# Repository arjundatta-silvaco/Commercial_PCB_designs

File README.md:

# Commercial PCB designs

A repository with circuits schematics and PCB designs of breakout boards.

Check out my blog: [https://semicon.world/](https://semicon.world/)

Support the blog and the GitHub: [https://razorpay.me/@semiconworld](https://razorpay.me/@semiconworld)

### License Notice: This repository is provided for personal study and educational reference. Research publication, commercial use, redistribution, and reuse of repository contents require prior permission. See the LICENSE file for details.

#### Currently in the Repository:

* LM2596S-adj Buck converter 9-12.9V to 5V 3A: Complete
* TP5100 Battery Charger 2S: Complete
* HX-2S-JH20: Complete
* HUSB238 USB-C Power Delivery: Complete
* ESP-32 DEVKIT V1 WROOM-32: Planned

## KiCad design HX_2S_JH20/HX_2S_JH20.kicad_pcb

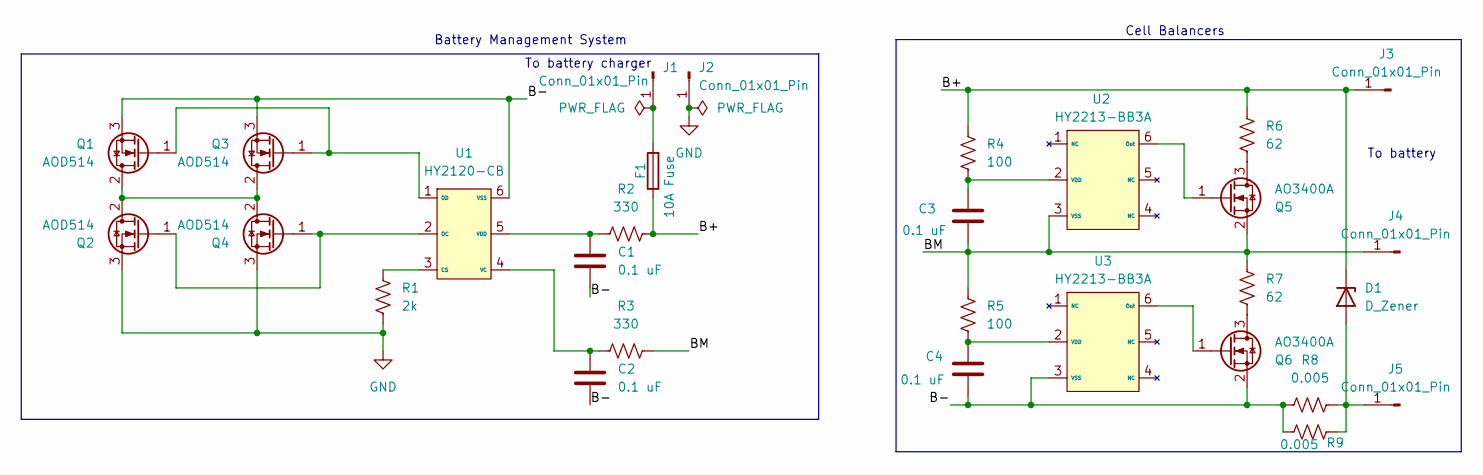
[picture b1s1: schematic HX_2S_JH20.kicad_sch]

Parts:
C1, C2, C3, C4: 0.1 uF; C_0603_1608Metric; Part number GRM188R61E104KA01D
D1: D_Zener; D_SOD-123; Part number MMSZ9V1T1G
F1: 10A Fuse; Fuse_0603_1608Metric; Part number 0685H9100-01
J1, J2, J3, J5: Conn_01x01_Pin; SolderWire-4sqmm_1x01_D3mm_OD6mm; Part number Bare pad
J4: Conn_01x01_Pin; SolderWire-2sqmm_1x01_D2mm_OD3.9mm; Part number Bare pad
Q1, Q2, Q3, Q4: AOD514; TO-252-2; Part number AOD514
Q5, Q6: AO3400A; SOT-23; Part number AO3400A
R1: 2k; R_0603_1608Metric; Part number ERJ-3EKF2001V
R2, R3: 330; R_0603_1608Metric; Part number ERJ-3GEYJ331V
R4, R5: 100; R_0603_1608Metric; Part number ESR03EZPF1000
R6, R7: 62; R_2512_6332Metric; Part number ERJ-1TYJ620U
R8, R9: 0.005; R_2512_6332Metric; Part number CRE2512-FZ-R005E-2
U1: HY2120-CB; SOT-23-6; Part number HY2120-CB
U2, U3: HY2213-BB3A; SOT-23-6; Part number HY2213-BB3A

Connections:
/B+: D1.1 (K), F1.1, J3.1 (Pin_1_1), R2.2, R4.1, R6.1
/B-: C1.2, C2.2, C4.2, Q1.3 (S), Q3.3 (S), Q6.2 (S), R8.1, R9.1, U1.6 (VSS), U3.3 (VSS)
/BM: C3.2, J4.1 (Pin_1_1), Q5.2 (S), R3.2, R5.1, R7.1, U2.3 (VSS)
GND: J2.1 (Pin_1_1), Q2.3 (S), Q4.3 (S), R1.2
unnamed: D1.2 (A), J5.1 (Pin_1_1), R8.2, R9.2
unnamed: F1.2, J1.1 (Pin_1_1)
unnamed: Q1.2 (D), Q2.2 (D), Q3.2 (D), Q4.2 (D)
unnamed: Q1.1 (G), Q3.1 (G), U1.1 (OD)
unnamed: Q2.1 (G), Q4.1 (G), U1.2 (OC)
unnamed: Q5.3 (D), R6.2
unnamed: Q5.1 (G), U2.6 (Out)
unnamed: Q6.3 (D), R7.2
unnamed: Q6.1 (G), U3.6 (Out)
unnamed: R1.1, U1.3 (CS)
unnamed: C2.1, R3.1, U1.4 (VC)
unnamed: C1.1, R2.1, U1.5 (VDD)
unnamed: C3.1, R4.2, U2.2 (VDD)
unnamed: C4.1, R5.2, U3.2 (VDD)

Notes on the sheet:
To battery
Battery Management System
To battery charger
Cell Balancers

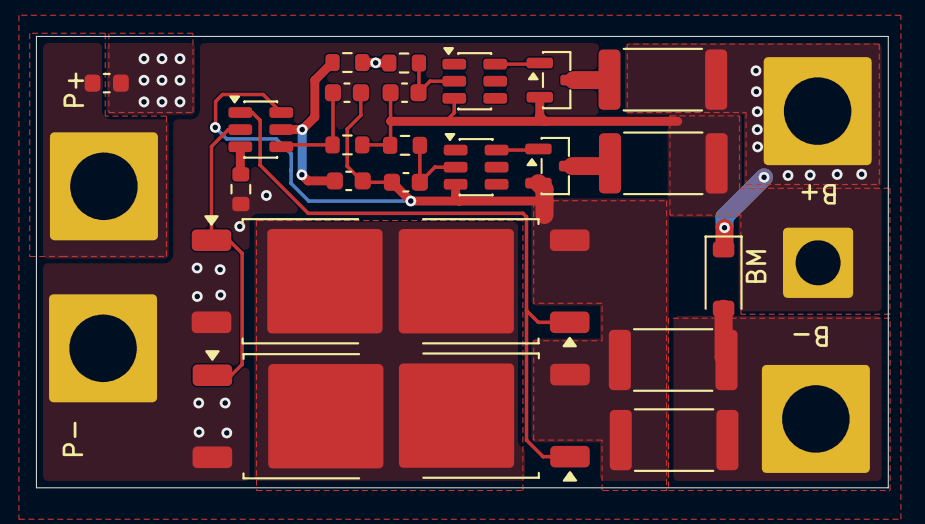
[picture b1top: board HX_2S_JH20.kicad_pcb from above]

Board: 2 copper layers, 47.3 x 25.1 mm, 29 parts (0 on the bottom side), 18 nets.

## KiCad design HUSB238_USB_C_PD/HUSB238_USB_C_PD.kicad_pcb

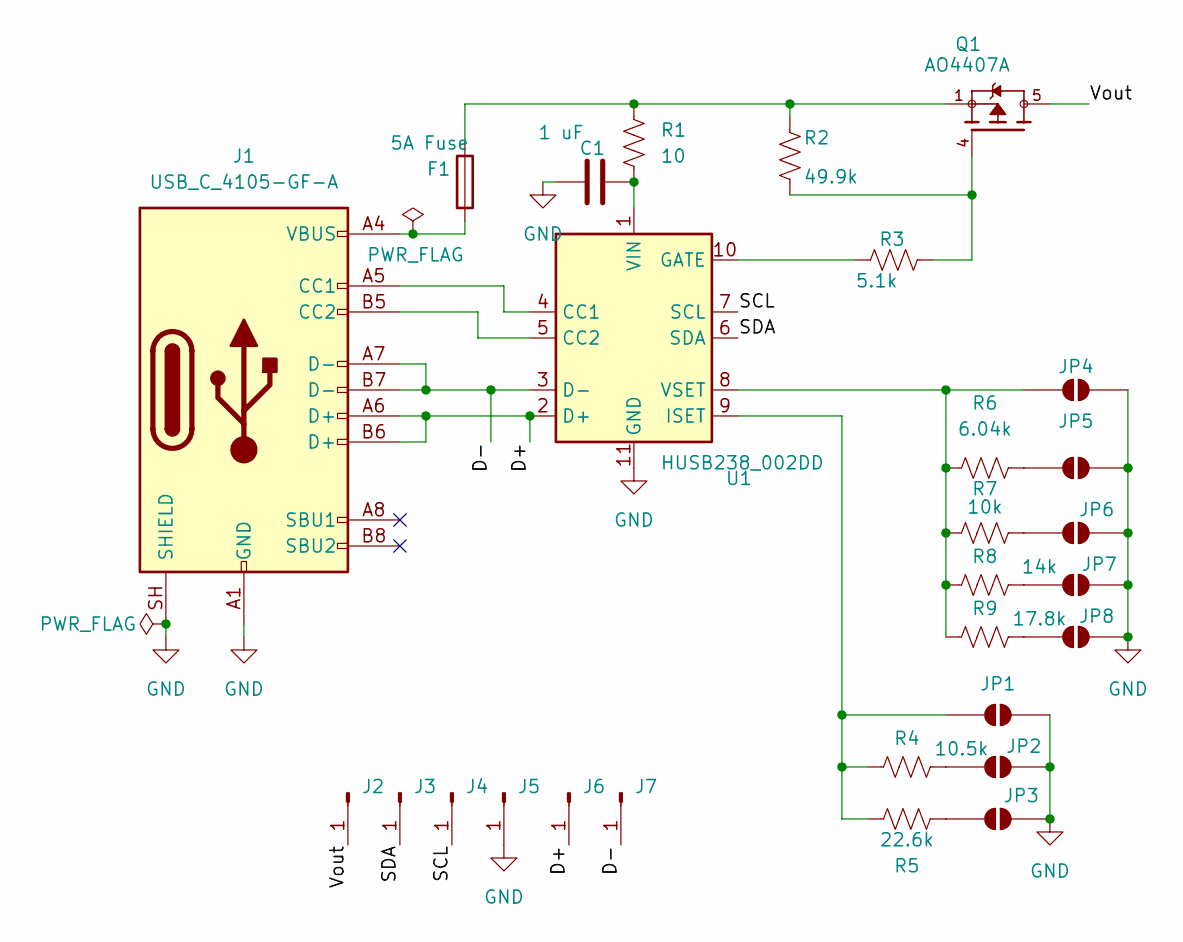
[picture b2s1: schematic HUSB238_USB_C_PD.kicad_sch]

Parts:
C1: 1 uF; C_0603_1608Metric; Part number CL10B105KA8VPJC
F1: 5A Fuse; Fuse_0603_1608Metric; Part number SF-0603FP500-2
J1: USB_C_4105-GF-A; USB_C_Receptacle_GCT_USB4105-xx-A_16P_TopMnt_Horizontal; Part number USB4105-GF-A
J2, J5: Conn_01x01_Pin; SolderWire-0.25sqmm_1x01_D0.65mm_OD1.7mm
J3, J4, J6, J7: Conn_01x01_Pin; SolderWire-0.1sqmm_1x01_D0.4mm_OD1mm
JP1, JP2, JP3, JP4, JP5, JP6, JP7, JP8: SolderJumper_2_Open; SolderJumper-2_P1.3mm_Open_TrianglePad1.0x1.5mm
Q1: AO4407A; SOIC-8_3.9x4.9mm_P1.27mm; Part number AO4407A
R1: 10; R_0603_1608Metric; Part number ERJ-U03F10R0V
R2: 49.9k; R_0603_1608Metric; Part number ERA-3AED4992V
R3: 5.1k; R_0603_1608Metric; Part number ERJ-3EKF5101V
R4: 10.5k; R_0603_1608Metric; Part number ERJ-3EKF1052V
R5: 22.6k; R_0603_1608Metric; Part number ERA-3AEB2262V
R6: 6.04k; R_0603_1608Metric; Part number ERJ-3EKF6041V
R7: 10k; R_0603_1608Metric; Part number ERJ-3EKF1002V
R8: 14k; R_0603_1608Metric; Part number ERJ-3EKF1402V
R9: 17.8k; R_0603_1608Metric; Part number ERJ-3EKF1782V
U1: HUSB238_002DD; WDFN-10-1EP_3x3mm_P0.5mm_EP1.8x2.5mm; Part number HUSB238_002DD

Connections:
/D+: J1.A6 (D+), J1.B6 (D+), J6.1 (Pin_1_1), U1.2 (D+)
/D-: J1.A7 (D-), J1.B7 (D-), J7.1 (Pin_1_1), U1.3 (D-)
/SCL: J4.1 (Pin_1_1), U1.7 (SCL)
/SDA: J3.1 (Pin_1_1), U1.6 (SDA)
/Vout: J2.1 (Pin_1_1), Q1.5, Q1.6, Q1.7, Q1.8
GND: C1.1, J1.A1 (GND), J1.A12 (GND), J1.B1 (GND), J1.B12 (GND), J1.SH (SHIELD), J5.1 (Pin_1_1), JP1.2 (B), JP2.2 (B), JP3.2 (B), JP4.2 (B), JP5.2 (B), JP6.2 (B), JP7.2 (B), JP8.2 (B), U1.11 (GND)
unnamed: F1.1, Q1.1, Q1.2, Q1.3, R1.2, R2.2
unnamed: F1.2, J1.A4 (VBUS), J1.A9 (VBUS), J1.B4 (VBUS), J1.B9 (VBUS)
unnamed: J1.A5 (CC1), U1.4 (CC1)
unnamed: J1.B5 (CC2), U1.5 (CC2)
unnamed: JP1.1 (A), R4.1, R5.1, U1.9 (ISET)
unnamed: JP2.1 (A), R4.2
unnamed: JP3.1 (A), R5.2
unnamed: JP4.1 (A), R6.1, R7.1, R8.1, R9.1, U1.8 (VSET)
unnamed: JP5.1 (A), R6.2
unnamed: JP6.1 (A), R7.2
unnamed: JP7.1 (A), R8.2
unnamed: JP8.1 (A), R9.2
unnamed: Q1.4, R2.1, R3.2
unnamed: R3.1, U1.10 (GATE)
unnamed: C1.2, R1.1, U1.1 (VIN)

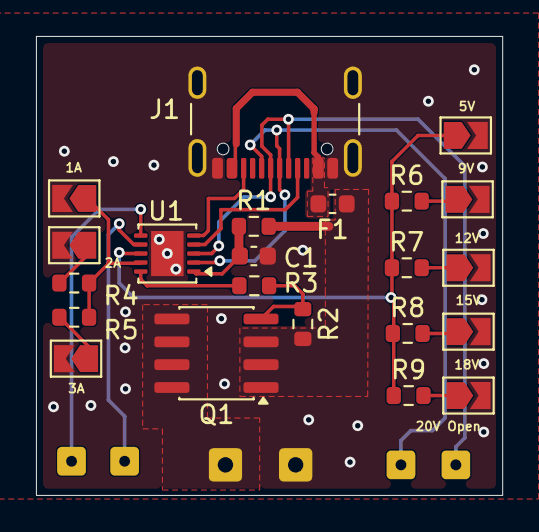
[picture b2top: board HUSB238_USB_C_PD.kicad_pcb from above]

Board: 2 copper layers, 25.9 x 25.5 mm, 28 parts (0 on the bottom side), 21 nets.

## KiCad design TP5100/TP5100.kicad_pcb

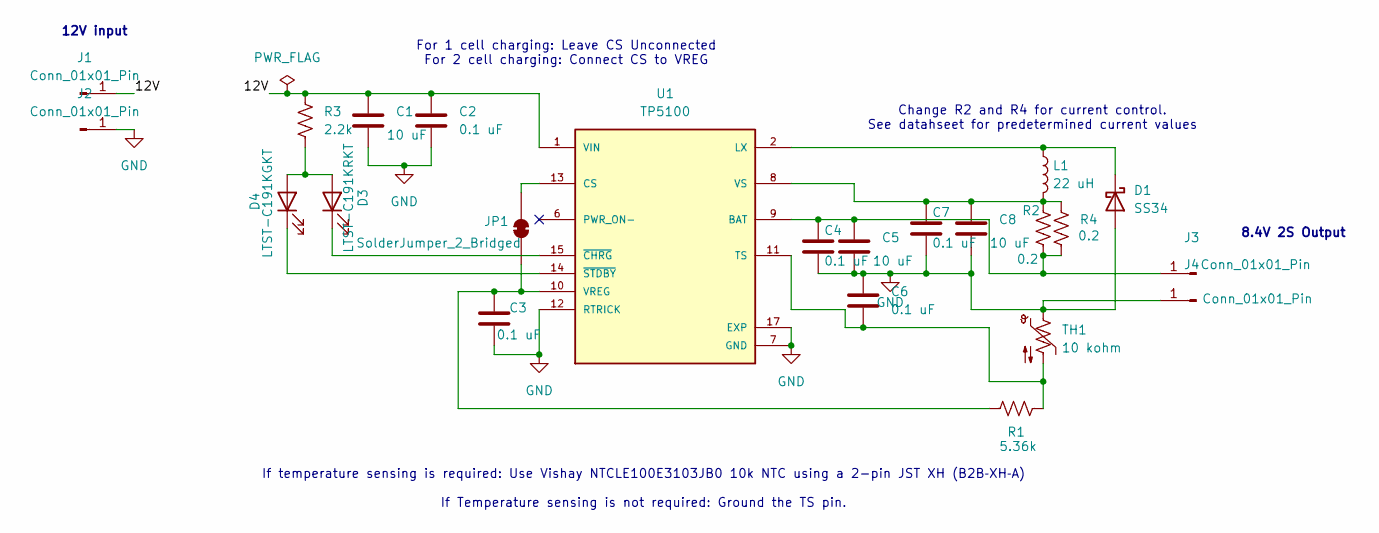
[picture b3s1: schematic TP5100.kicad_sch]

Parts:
C1: 10 uF; C_1206_3216Metric; Part number CL31B106KAHNNNE
C2, C3, C4, C6, C7: 0.1 uF; C_0603_1608Metric; Part number GRM188R61E104KA01D
C5, C8: 10 uF; C_0603_1608Metric; Part number GRM188R61E106KA73D
D1: SS34; D_SMA; Part number SS34
D3: LTST-C191KRKT; LED_0603_1608Metric; Part number LTST-C191KRKT
D4: LTST-C191KGKT; LED_0603_1608Metric; Part number LTST-C191KGKT
J1, J2, J3, J4: Conn_01x01_Pin; SolderWire-1sqmm_1x01_D1.4mm_OD2.7mm; Part number Bare pad
JP1: SolderJumper_2_Bridged; SolderJumper-2_P1.3mm_Open_RoundedPad1.0x1.5mm
L1: 22 uH; L_Wuerth_WE-PD-Typ-LS; Part number 744770122
R1: 5.36k; R_0603_1608Metric; Part number ERJ-3EKF5361V
R2, R4: 0.2; R_1206_3216Metric; Part number PE1206FRF470R2L
R3: 2.2k; R_0603_1608Metric; Part number ERJ-3EKF2201V
TH1: 10 kohm; JST_XH_B2B-XH-A_1x02_P2.50mm_Vertical; Part number B2B-XH-A
U1: TP5100; QFN65P400X400X90-17N; Part number TP5100

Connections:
/12V: C1.1, C2.1, J1.1 (Pin_1_1), R3.1, U1.1 (VIN), U1.4 (VIN), U1.5 (VIN), U1.16 (VIN)
GND: C1.2, C2.2, C3.2, C4.2, C5.2, C6.1, C7.2, C8.2, D1.2 (A), J2.1 (Pin_1_1), J4.1 (Pin_1_1), TH1.1, U1.7 (GND), U1.12 (RTRICK), U1.17 (EXP)
unnamed: D1.1 (K), L1.1, U1.2 (LX), U1.3 (LX)
unnamed: D3.2 (A), D4.2 (A), R3.2
unnamed: D3.1 (K), U1.15 (~CHRG)
unnamed: D4.1 (K), U1.14 (~STDBY)
unnamed: C4.1, C5.1, J3.1 (Pin_1_1), R2.2, R4.2, U1.9 (BAT)
unnamed: C3.1, JP1.1 (A), R1.2, U1.10 (VREG)
unnamed: JP1.2 (B), U1.13 (CS)
unnamed: C6.2, R1.1, TH1.2, U1.11 (TS)
unnamed: C7.1, C8.1, L1.2, R2.1, R4.1, U1.8 (VS)

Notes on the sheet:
12V input
For 1 cell charging: Leave CS Unconnected For 2 cell charging: Connect CS to VREG
Change R2 and R4 for current control. See datahseet for predetermined current values
8.4V 2S Output
If temperature sensing is required: Use Vishay NTCLE100E3103JB0 10k NTC using a 2-pin JST XH (B2B‑XH‑A) If Temperature sensing is not required: Ground the TS pin.

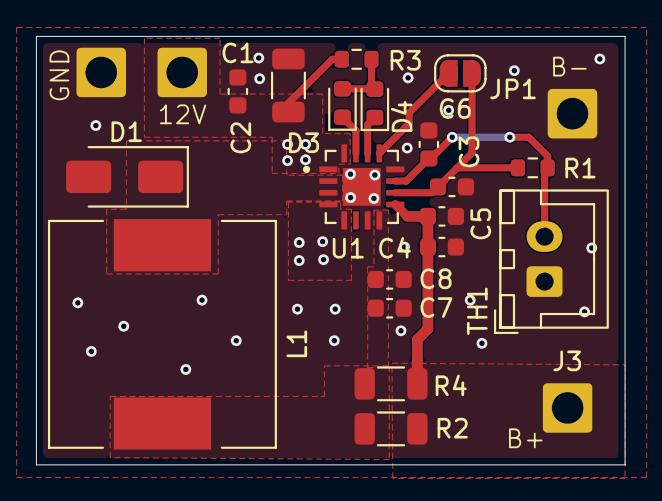
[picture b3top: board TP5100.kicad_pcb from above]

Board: 2 copper layers, 32.7 x 23.8 mm, 23 parts (0 on the bottom side), 11 nets.

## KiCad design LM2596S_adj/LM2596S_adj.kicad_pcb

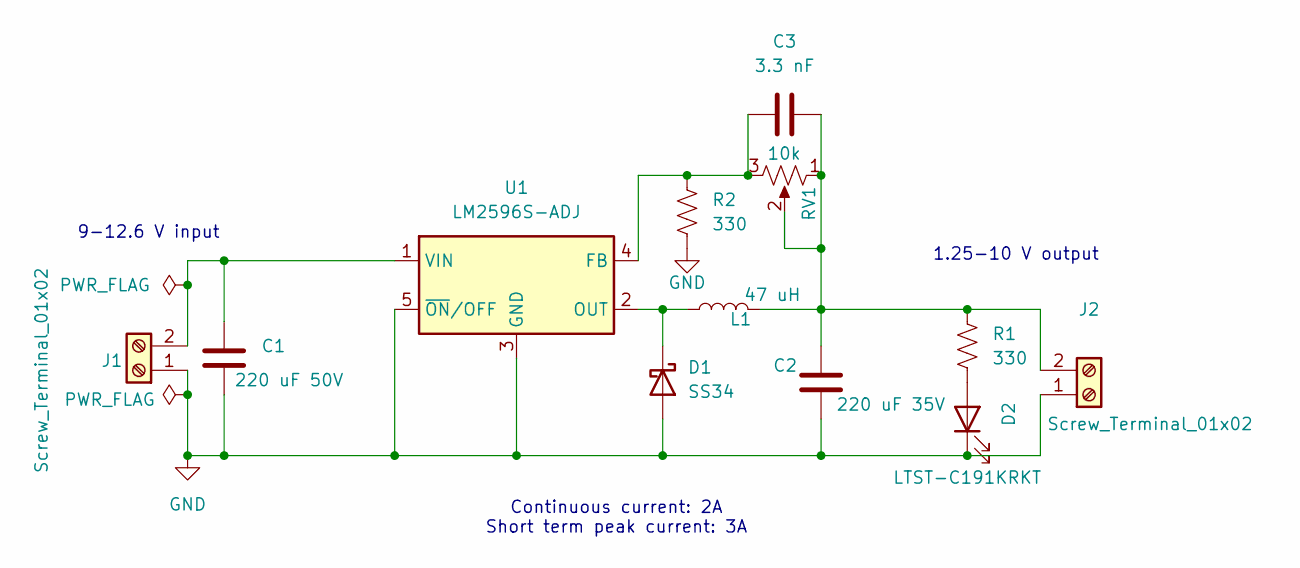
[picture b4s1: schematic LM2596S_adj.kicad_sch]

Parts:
C1: 220 uF 50V; CAP_EEHZS1H221P; Part number EEH-ZS1H221P
C2: 220 uF 35V; CAP_EEEFK1V221P; Part number EEE-FK1V221P
C3: 3.3 nF; C_0603_1608Metric; Part number 0603B332K101SD
D1: SS34; D_SMA; Part number SS34
D2: LTST-C191KRKT; LED_0603_1608Metric; Part number LTST-C191KRKT
J1, J2: Screw_Terminal_01x02; TerminalBlock_RND_205-00001_1x02_P5.00mm_Horizontal; Part number 691137710002
L1: 47 uH; L_Wuerth_WE-PD-Typ-LS; Part number 7447709470
R1, R2: 330; R_0603_1608Metric; Part number RC0603FR-07330RL
RV1: 10k; TRIM_3296W-1-103; Part number 3296W-1-103
U1: LM2596S-ADJ; TO-263-5_TabPin3; Part number LM2596S-ADJ

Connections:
GND: C1.2, C2.2, D1.2 (A), D2.1 (K), J1.1, J2.1, R2.2, U1.3 (GND), U1.5 (~ON/OFF)
unnamed: D1.1 (K), L1.1, U1.2 (OUT)
unnamed: D2.2 (A), R1.2
unnamed: C1.1, J1.2, U1.1 (VIN)
unnamed: C2.1, C3.2, J2.2, L1.2, R1.1, RV1.1, RV1.2
unnamed: C3.1, R2.1, RV1.3, U1.4 (FB)

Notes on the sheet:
1.25-10 V output
9-12.6 V input
Continuous current: 2A Short term peak current: 3A

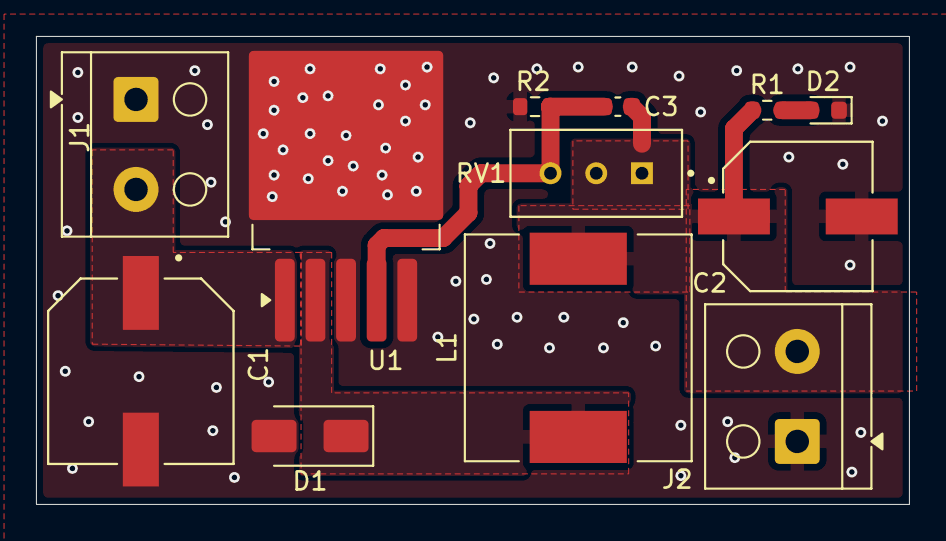
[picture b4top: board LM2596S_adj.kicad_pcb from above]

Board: 2 copper layers, 48.5 x 26.0 mm, 12 parts (0 on the bottom side), 6 nets.
